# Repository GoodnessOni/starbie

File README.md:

# starbie
Starbie, a motion-controlled digital pet PCB (ESP32-C3, OLED, MPU6050, DHT11

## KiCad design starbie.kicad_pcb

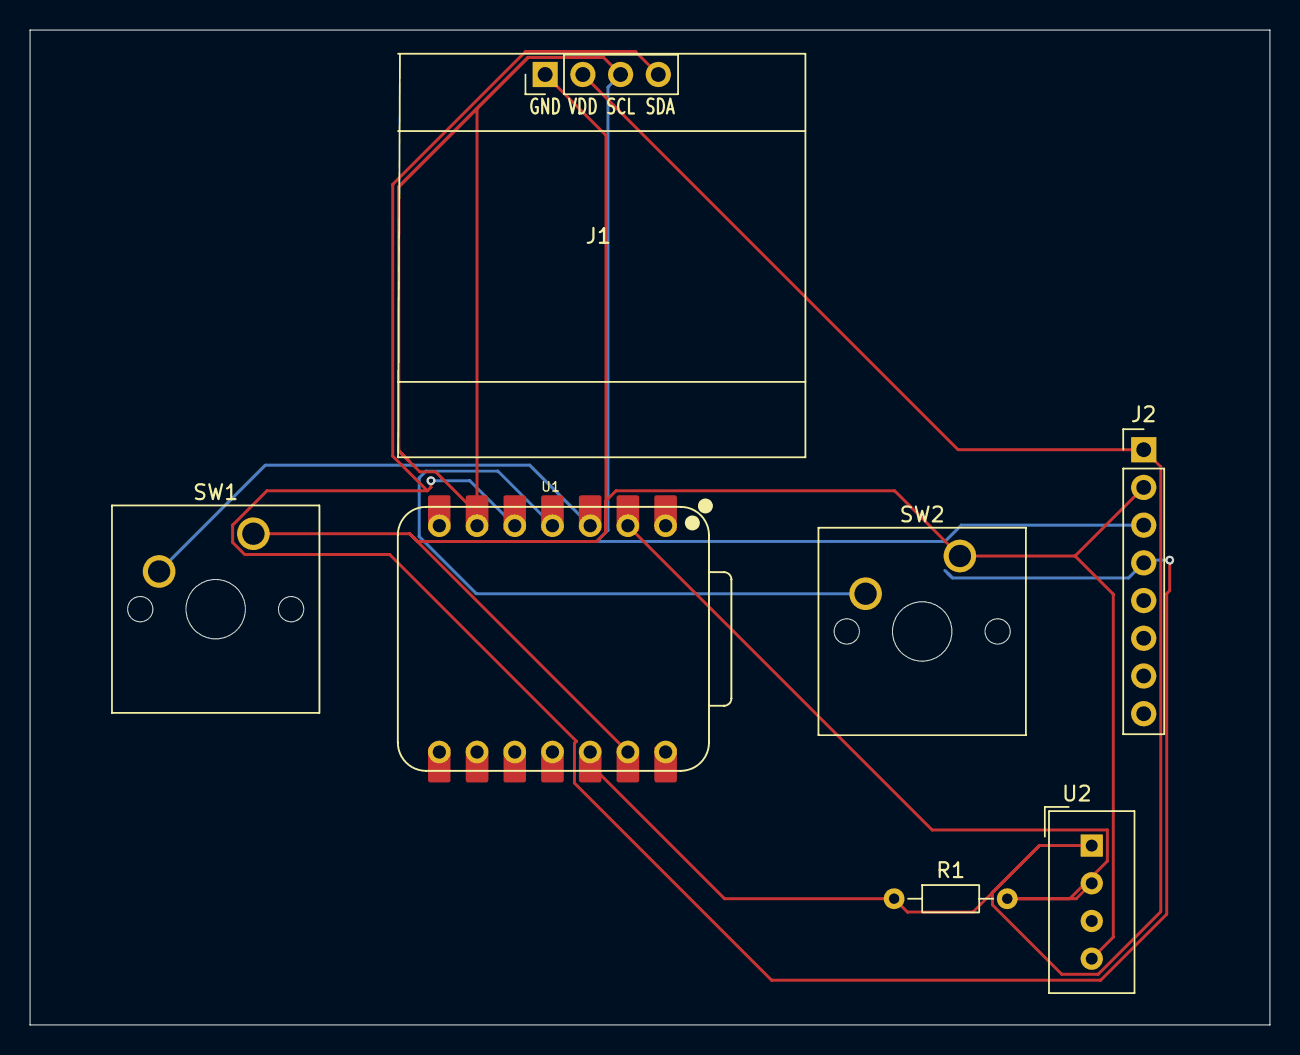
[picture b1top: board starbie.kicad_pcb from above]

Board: 2 copper layers, 83.5 x 67.0 mm, 7 parts (0 on the bottom side), 7 nets.

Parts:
J1: Conn_01x04; Display_128x64_096_I2C
J2: Conn_01x08_Pin; PinHeader_1x08_P2.54mm_Vertical
R1: 10K; R_Axial_DIN0204_L3.6mm_D1.6mm_P7.62mm_Horizontal
SW1, SW2: SW_Push; SW_Cherry_MX_1.00u_PCB
U1: XIAO-ESP32-C3-SMD; XIAO-ESP32-C6-DIP
U2: DHT11; Aosong_DHT11_5.5x12.0_P2.54mm

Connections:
+3.3V: J1.2, J2.1, R1.1, U1.12 (3V3_OUT), U2.1 (VDD)
/BTN1: SW1.2, U1.3 (D2)
/BTN2: SW2.2, U1.4 (D3)
/DHT: R1.2, U1.2 (D1), U2.2 (DATA)
/SCL: J1.3, J2.3, U1.6 (D5)
/SDA: J1.4, J2.4, U1.5 (D4)
GND: J1.1, J2.2, SW1.1, SW2.1, U1.13 (GND), U2.4 (GND)
